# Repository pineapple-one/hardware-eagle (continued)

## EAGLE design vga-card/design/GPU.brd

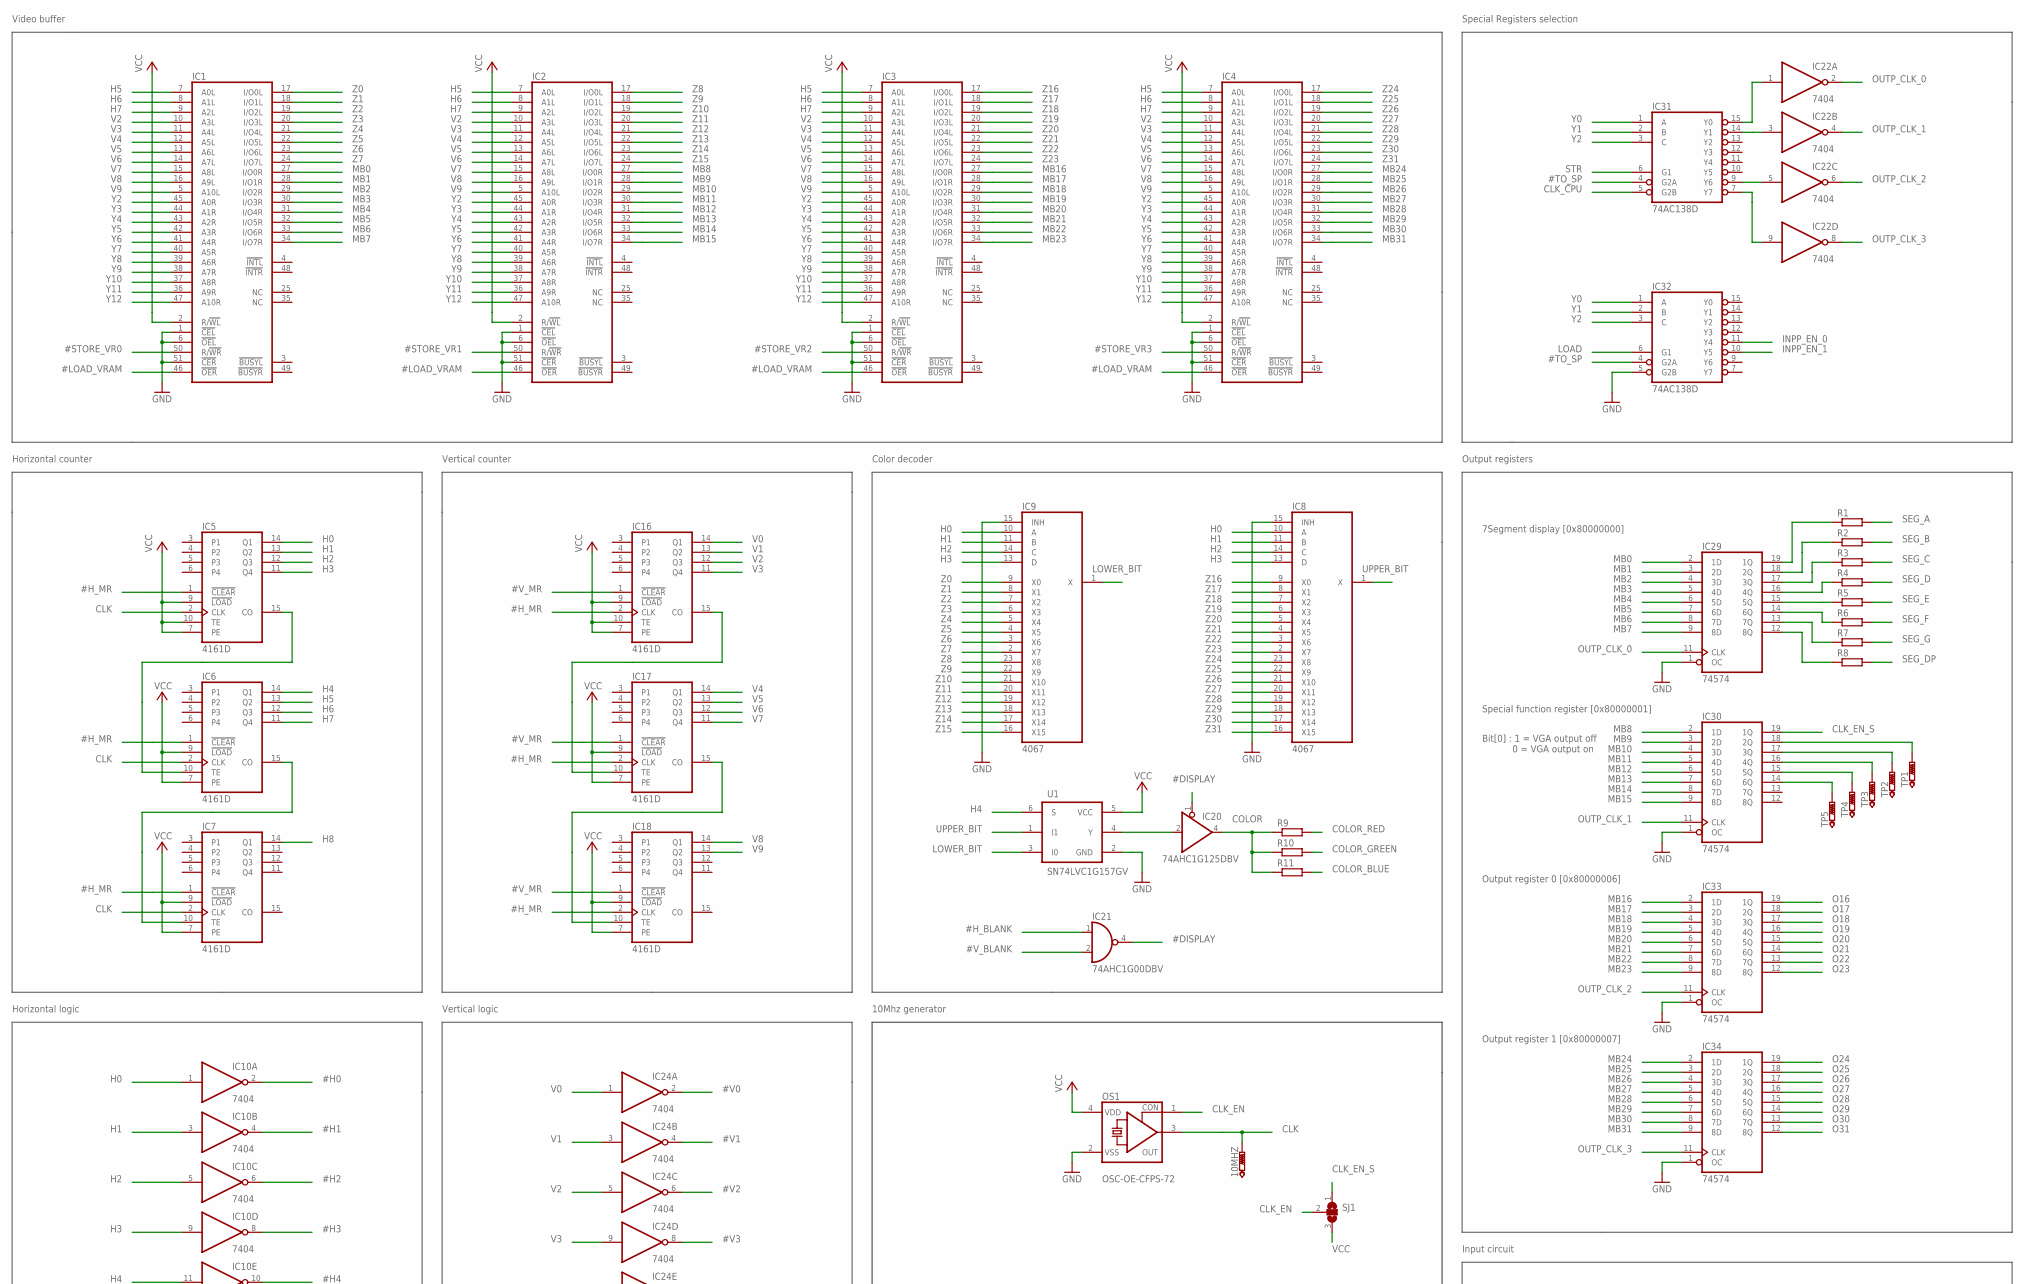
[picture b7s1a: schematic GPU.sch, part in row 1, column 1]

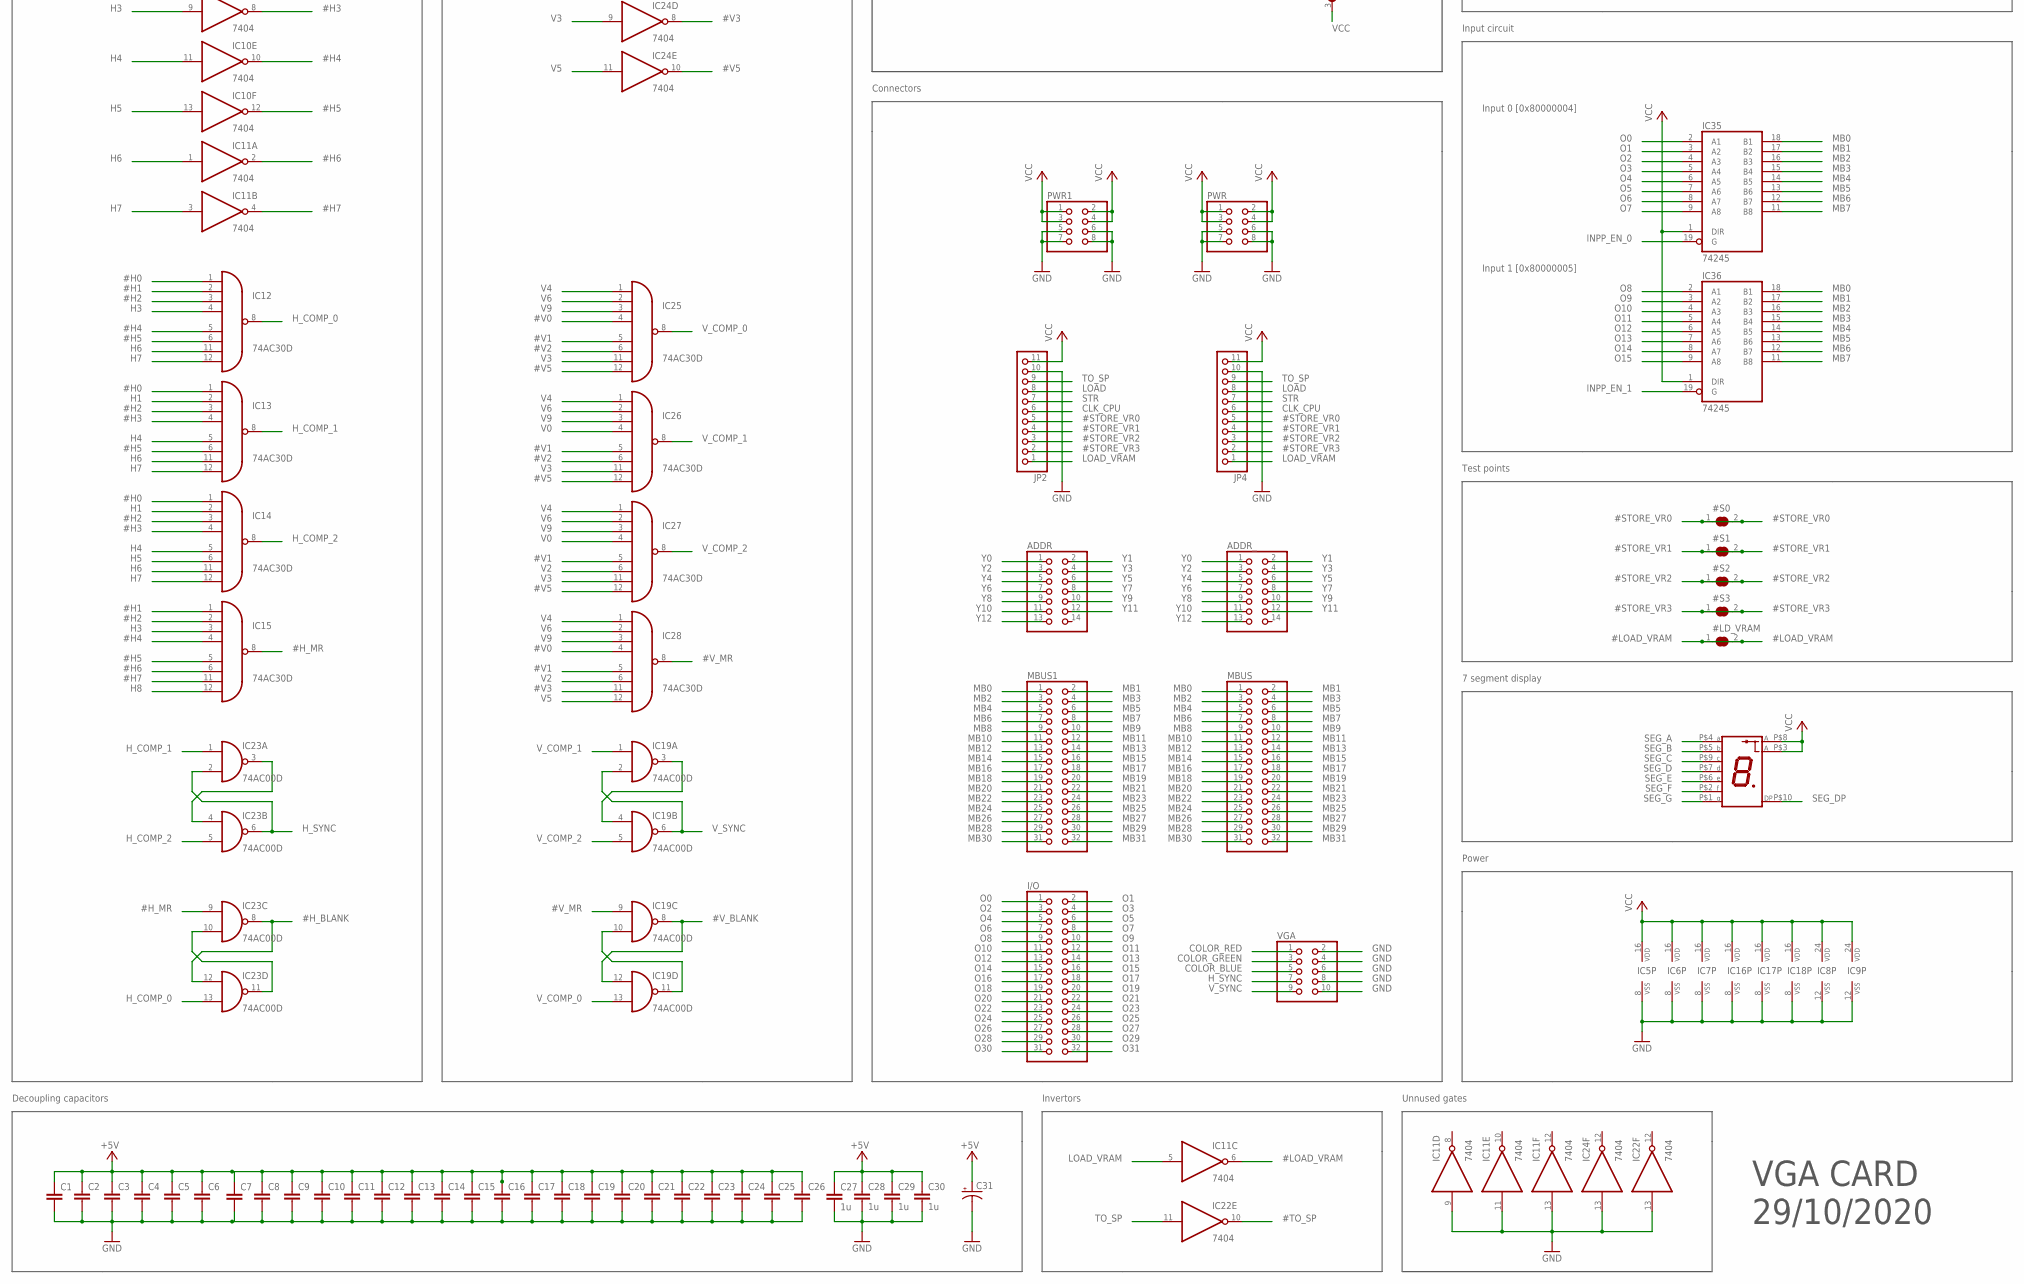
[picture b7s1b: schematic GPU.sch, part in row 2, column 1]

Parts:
10MHZ: PTR1B2,54; B2,54
#LD_VRAM: SJ
#S0, #S1, #S2, #S3: SJ
ADDR: PINHD-2X7; 2X07
ADDR_: PINHD-2X7; 2X07
C1, C2, C3, C4, C5, C6, C7, C8, C9, C10, C11, C12, C13, C14, C15, C16, C17, C18, C19, C20, C21, C22, C23, C24, C25, C26: C-EUC0805; C0805
C27, C28, C29, C30: 1u; C0805
C31: CAPACITOR-P153CLV-1010; 153CLV-1010
I/O: PINHD-2X16; 2X16
IC1, IC2, IC3, IC4: 71321L; L52-1
IC5, IC6, IC7, IC16, IC17, IC18: 4161D; SO16
IC8, IC9: 4067; TSSOP24
IC10, IC11, IC22, IC24: 7404; TSSOP14
IC12, IC13, IC14, IC15, IC25, IC26, IC27, IC28: 74AC30D; SO14
IC19, IC23: 74AC00D; SO14
IC20: 74AHC1G125DBV; SOT23-5
IC21: 74AHC1G00DBV; SOT23-5
IC29, IC30, IC33, IC34: 74574; TSSOP20
IC31, IC32: 74AC138D; SO16
IC35, IC36: 74245; TSSOP20
JP2, JP4: PINHD-1X11; 1X11
MBUS, MBUS1: PINHD-2X16; 2X16
OS1: OSC-OE-CFPS-72; 7.2X5.2-4-PAD
PWR, PWR1: PINHD-2X4; 2X04
R1, R2, R3, R4, R5, R6, R7, R8, R9, R10, R11: R-EU_R0805; R0805
SJ1: SJ2W; SJ_2
TP1, TP2, TP3, TP4, TP5: PTR1B1,27; B1,27
U1: SN74LVC1G157GV; SOT457
U$1: OPS-S5621YG
VGA: PINHD-2X5; 2X05

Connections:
#DISPLAY: IC20.1 (OE), IC21.4 (O)
#H0: IC10.2 (O), IC12.1 (I0), IC13.1 (I0), IC14.1 (I0)
#H1: IC10.4 (O), IC12.2 (I1), IC15.1 (I0)
#H2: IC10.6 (O), IC12.3 (I2), IC13.3 (I2), IC14.3 (I2), IC15.2 (I1)
#H3: IC10.8 (O), IC13.4 (I3), IC14.4 (I3)
#H4: IC10.10 (O), IC12.5 (I4), IC15.4 (I3)
#H5: IC10.12 (O), IC12.6 (I5), IC13.6 (I5), IC15.5 (I4)
#H6: IC11.2 (O), IC15.6 (I5)
#H7: IC11.4 (O), IC15.11 (I6)
#H_BLANK: IC21.1 (I0), IC23.8 (O), IC23.12 (I0)
#H_MR: IC5.1 (!CLEAR), IC6.1 (!CLEAR), IC7.1 (!CLEAR), IC15.8 (O), IC16.2 (CLK), IC17.2 (CLK), IC18.2 (CLK), IC23.9 (I0)
#LOAD_VRAM: #LD_VRAM.1, #LD_VRAM.2, IC1.46 (!OER), IC2.46 (!OER), IC3.46 (!OER), IC4.46 (!OER), IC11.6 (O)
#STORE_VR0: #S0.1, #S0.2, IC1.50 (R/!WR), JP2.5, JP4.5
#STORE_VR1: #S1.1, #S1.2, IC2.50 (R/!WR), JP2.4, JP4.4
#STORE_VR2: #S2.1, #S2.2, IC3.50 (R/!WR), JP2.3, JP4.3
#STORE_VR3: #S3.1, #S3.2, IC4.50 (R/!WR), JP2.2, JP4.2
#TO_SP: IC22.10 (O), IC31.4 (G2A), IC32.4 (G2A)
#V0: IC24.2 (O), IC25.4 (I3), IC28.4 (I3)
#V1: IC24.4 (O), IC25.5 (I4), IC26.5 (I4), IC27.5 (I4), IC28.5 (I4)
#V2: IC24.6 (O), IC25.6 (I5), IC26.6 (I5)
#V3: IC24.8 (O), IC28.11 (I6)
#V5: IC24.10 (O), IC25.12 (I7), IC26.12 (I7), IC27.12 (I7)
#V_BLANK: IC19.8 (O), IC19.12 (I0), IC21.2 (I1)
#V_MR: IC16.1 (!CLEAR), IC17.1 (!CLEAR), IC18.1 (!CLEAR), IC19.9 (I0), IC28.8 (O)
CLK: 10MHZ.TP, IC5.2 (CLK), IC6.2 (CLK), IC7.2 (CLK), OS1.3 (OUT)
CLK_CPU: IC31.5 (G2B), JP2.6, JP4.6
CLK_EN: OS1.1 (CON), SJ1.2
CLK_EN_S: IC30.19 (1Q), SJ1.1
COLOR: IC20.4 (O), R9.1, R10.1, R11.1
COLOR_BLUE: R11.2, VGA.5
COLOR_GREEN: R10.2, VGA.3
COLOR_RED: R9.2, VGA.1
GND: C1.2, C2.2, C3.2, C4.2, C5.2, C6.2, C7.2, C8.2, C9.2, C10.2, C11.2, C12.2, C13.2, C14.2, C15.2, C16.2, C17.2, C18.2, C19.2, C20.2, C21.2, C22.2, C23.2, C24.2, C25.2, C26.2, C27.2, C28.2, C29.2, C30.2, C31.-, IC1.1 (!CEL), IC1.6 (!OEL), IC1.26 (GND), IC1.51 (!CER), IC2.1 (!CEL), IC2.6 (!OEL), IC2.26 (GND), IC2.51 (!CER), IC3.1 (!CEL), IC3.6 (!OEL), IC3.26 (GND), IC3.51 (!CER), IC4.1 (!CEL), IC4.6 (!OEL), IC4.26 (GND), IC4.51 (!CER), IC5.8 (VSS), IC6.8 (VSS), IC7.8 (VSS), IC8.12 (VSS), IC8.15 (INH), IC9.12 (VSS), IC9.15 (INH), IC10.7 (GND), IC11.7 (GND), IC11.9 (I), IC11.11 (I), IC11.13 (I), IC12.7 (GND), IC13.7 (GND), IC14.7 (GND), IC15.7 (GND), IC16.8 (VSS), IC17.8 (VSS), IC18.8 (VSS), IC19.7 (GND), IC20.3 (GND), IC21.3 (GND), IC22.7 (GND), IC22.13 (I), IC23.7 (GND), IC24.7 (GND), IC24.13 (I), IC25.7 (GND), IC26.7 (GND), IC27.7 (GND), IC28.7 (GND), IC29.1 (OC), IC29.10 (GND), IC30.1 (OC), IC30.10 (GND), IC31.8 (GND), IC32.5 (G2B), IC32.8 (GND), IC33.1 (OC), IC33.10 (GND), IC34.1 (OC), IC34.10 (GND), IC35.10 (GND), IC36.10 (GND), JP2.10, JP4.10, OS1.2 (VSS), PWR.5, PWR.6, PWR.7, PWR.8, PWR1.5, PWR1.6, PWR1.7, PWR1.8, U1.2 (GND), VGA.2, VGA.4, VGA.6, VGA.8, VGA.10
H0: IC5.14 (Q1), IC8.10 (A), IC9.10 (A), IC10.1 (I)
H1: IC5.13 (Q2), IC8.11 (B), IC9.11 (B), IC10.3 (I), IC13.2 (I1), IC14.2 (I1)
H2: IC5.12 (Q3), IC8.14 (C), IC9.14 (C), IC10.5 (I)
H3: IC5.11 (Q4), IC8.13 (D), IC9.13 (D), IC10.9 (I), IC12.4 (I3), IC15.3 (I2)
H4: IC6.14 (Q1), IC10.11 (I), IC13.5 (I4), IC14.5 (I4), U1.6 (S)
H5: IC1.7 (A0L), IC2.7 (A0L), IC3.7 (A0L), IC4.7 (A0L), IC6.13 (Q2), IC10.13 (I), IC14.6 (I5)
H6: IC1.8 (A1L), IC2.8 (A1L), IC3.8 (A1L), IC4.8 (A1L), IC6.12 (Q3), IC11.1 (I), IC12.11 (I6), IC13.11 (I6), IC14.11 (I6)
H7: IC1.9 (A2L), IC2.9 (A2L), IC3.9 (A2L), IC4.9 (A2L), IC6.11 (Q4), IC11.3 (I), IC12.12 (I7), IC13.12 (I7), IC14.12 (I7)
H8: IC7.14 (Q1), IC15.12 (I7)
H_COMP_0: IC12.8 (O), IC23.13 (I1)
H_COMP_1: IC13.8 (O), IC23.1 (I0)
H_COMP_2: IC14.8 (O), IC23.5 (I1)
H_SYNC: IC23.2 (I1), IC23.6 (O), VGA.7
H_SYNC1: IC23.10 (I1), IC23.11 (O)
H_SYNC2: IC19.10 (I1), IC19.11 (O)
INPP_EN_0: IC32.11 (Y4), IC35.19 (G)
INPP_EN_1: IC32.10 (Y5), IC36.19 (G)
LOAD: IC32.6 (G1), JP2.8, JP4.8
LOAD_VRAM: IC11.5 (I), JP2.1, JP4.1
LOWER_BIT: IC9.1 (X), U1.3 (I0)
MB0: IC1.27 (I/O0R), IC29.2 (1D), IC35.18 (B1), IC36.18 (B1), MBUS.1, MBUS1.1
MB1: IC1.28 (I/O1R), IC29.3 (2D), IC35.17 (B2), IC36.17 (B2), MBUS.2, MBUS1.2
MB2: IC1.29 (I/O2R), IC29.4 (3D), IC35.16 (B3), IC36.16 (B3), MBUS.3, MBUS1.3
MB3: IC1.30 (I/O3R), IC29.5 (4D), IC35.15 (B4), IC36.15 (B4), MBUS.4, MBUS1.4
MB4: IC1.31 (I/O4R), IC29.6 (5D), IC35.14 (B5), IC36.14 (B5), MBUS.5, MBUS1.5
MB5: IC1.32 (I/O5R), IC29.7 (6D), IC35.13 (B6), IC36.13 (B6), MBUS.6, MBUS1.6
MB6: IC1.33 (I/O6R), IC29.8 (7D), IC35.12 (B7), IC36.12 (B7), MBUS.7, MBUS1.7
MB7: IC1.34 (I/O7R), IC29.9 (8D), IC35.11 (B8), IC36.11 (B8), MBUS.8, MBUS1.8
MB8: IC2.27 (I/O0R), IC30.2 (1D), MBUS.9, MBUS1.9
MB9: IC2.28 (I/O1R), IC30.3 (2D), MBUS.10, MBUS1.10
MB10: IC2.29 (I/O2R), IC30.4 (3D), MBUS.11, MBUS1.11
MB11: IC2.30 (I/O3R), IC30.5 (4D), MBUS.12, MBUS1.12
MB12: IC2.31 (I/O4R), IC30.6 (5D), MBUS.13, MBUS1.13
MB13: IC2.32 (I/O5R), IC30.7 (6D), MBUS.14, MBUS1.14
MB14: IC2.33 (I/O6R), IC30.8 (7D), MBUS.15, MBUS1.15
MB15: IC2.34 (I/O7R), IC30.9 (8D), MBUS.16, MBUS1.16
MB16: IC3.27 (I/O0R), IC33.2 (1D), MBUS.17, MBUS1.17
MB17: IC3.28 (I/O1R), IC33.3 (2D), MBUS.18, MBUS1.18
MB18: IC3.29 (I/O2R), IC33.4 (3D), MBUS.19, MBUS1.19
MB19: IC3.30 (I/O3R), IC33.5 (4D), MBUS.20, MBUS1.20
MB20: IC3.31 (I/O4R), IC33.6 (5D), MBUS.21, MBUS1.21
MB21: IC3.32 (I/O5R), IC33.7 (6D), MBUS.22, MBUS1.22
MB22: IC3.33 (I/O6R), IC33.8 (7D), MBUS.23, MBUS1.23
MB23: IC3.34 (I/O7R), IC33.9 (8D), MBUS.24, MBUS1.24
MB24: IC4.27 (I/O0R), IC34.2 (1D), MBUS.25, MBUS1.25
MB25: IC4.28 (I/O1R), IC34.3 (2D), MBUS.26, MBUS1.26
MB26: IC4.29 (I/O2R), IC34.4 (3D), MBUS.27, MBUS1.27
MB27: IC4.30 (I/O3R), IC34.5 (4D), MBUS.28, MBUS1.28
MB28: IC4.31 (I/O4R), IC34.6 (5D), MBUS.29, MBUS1.29
MB29: IC4.32 (I/O5R), IC34.7 (6D), MBUS.30, MBUS1.30
MB30: IC4.33 (I/O6R), IC34.8 (7D), MBUS.31, MBUS1.31
MB31: IC4.34 (I/O7R), IC34.9 (8D), MBUS.32, MBUS1.32
unnamed: IC23.3 (O), IC23.4 (I0)
unnamed: IC5.15 (CO), IC6.10 (TE)
unnamed: IC6.15 (CO), IC7.10 (TE)
unnamed: IC16.15 (CO), IC17.10 (TE)
unnamed: IC17.15 (CO), IC18.10 (TE)
unnamed: IC19.3 (O), IC19.4 (I0)
unnamed: IC20.2 (I), U1.4 (Y)
unnamed: IC22.1 (I), IC31.15 (Y0)
unnamed: IC30.18 (2Q), TP1.TP
unnamed: IC29.19 (1Q), R1.1
unnamed: IC22.9 (I), IC31.7 (Y7)
unnamed: IC29.18 (2Q), R2.1
unnamed: IC29.17 (3Q), R3.1
unnamed: IC29.16 (4Q), R4.1
unnamed: IC29.15 (5Q), R5.1
unnamed: IC29.14 (6Q), R6.1
unnamed: IC22.5 (I), IC31.9 (Y6)
unnamed: IC29.13 (7Q), R7.1
unnamed: IC29.12 (8Q), R8.1
unnamed: IC22.3 (I), IC31.14 (Y1)
unnamed: IC30.17 (3Q), TP2.TP
unnamed: IC30.16 (4Q), TP3.TP
unnamed: IC30.15 (5Q), TP4.TP
unnamed: IC30.14 (6Q), TP5.TP
O0: I/O.1, IC35.2 (A1)
O1: I/O.2, IC35.3 (A2)
O2: I/O.3, IC35.4 (A3)
O3: I/O.4, IC35.5 (A4)
O4: I/O.5, IC35.6 (A5)
O5: I/O.6, IC35.7 (A6)
O6: I/O.7, IC35.8 (A7)
O7: I/O.8, IC35.9 (A8)
O8: I/O.9, IC36.2 (A1)
O9: I/O.10, IC36.3 (A2)
O10: I/O.11, IC36.4 (A3)
O11: I/O.12, IC36.5 (A4)
O12: I/O.13, IC36.6 (A5)
O13: I/O.14, IC36.7 (A6)
O14: I/O.15, IC36.8 (A7)
O15: I/O.16, IC36.9 (A8)
O16: I/O.17, IC33.19 (1Q)
O17: I/O.18, IC33.18 (2Q)
O18: I/O.19, IC33.17 (3Q)
O19: I/O.20, IC33.16 (4Q)
O20: I/O.21, IC33.15 (5Q)
O21: I/O.22, IC33.14 (6Q)
O22: I/O.23, IC33.13 (7Q)
O23: I/O.24, IC33.12 (8Q)
O24: I/O.25, IC34.19 (1Q)
O25: I/O.26, IC34.18 (2Q)
O26: I/O.27, IC34.17 (3Q)
O27: I/O.28, IC34.16 (4Q)
O28: I/O.29, IC34.15 (5Q)
O29: I/O.30, IC34.14 (6Q)
O30: I/O.31, IC34.13 (7Q)
O31: I/O.32, IC34.12 (8Q)
OUTP_CLK_0: IC22.2 (O), IC29.11 (CLK)
OUTP_CLK_1: IC22.4 (O), IC30.11 (CLK)
OUTP_CLK_2: IC22.6 (O), IC33.11 (CLK)
OUTP_CLK_3: IC22.8 (O), IC34.11 (CLK)
SEG_A: R1.2, U$1.P$4 (A)
SEG_B: R2.2, U$1.P$5 (B)
SEG_C: R3.2, U$1.P$9 (C)
SEG_D: R4.2, U$1.P$7 (D)
SEG_DP: R8.2, U$1.P$10 (DP)
SEG_E: R5.2, U$1.P$6 (E)
SEG_F: R6.2, U$1.P$2 (F)
SEG_G: R7.2, U$1.P$1 (G)
STR: IC31.6 (G1), JP2.7, JP4.7
TO_SP: IC22.11 (I), JP2.9, JP4.9
UPPER_BIT: IC8.1 (X), U1.1 (I1)
V0: IC16.14 (Q1), IC24.1 (I), IC26.4 (I3), IC27.4 (I3)
V1: IC16.13 (Q2), IC24.3 (I)
V2: IC1.10 (A3L), IC2.10 (A3L), IC3.10 (A3L), IC4.10 (A3L), IC16.12 (Q3), IC24.5 (I), IC27.6 (I5), IC28.6 (I5)
V3: IC1.11 (A4L), IC2.11 (A4L), IC3.11 (A4L), IC4.11 (A4L), IC16.11 (Q4), IC24.9 (I), IC25.11 (I6), IC26.11 (I6), IC27.11 (I6)
V4: IC1.12 (A5L), IC2.12 (A5L), IC3.12 (A5L), IC4.12 (A5L), IC17.14 (Q1), IC25.1 (I0), IC26.1 (I0), IC27.1 (I0), IC28.1 (I0)
V5: IC1.13 (A6L), IC2.13 (A6L), IC3.13 (A6L), IC4.13 (A6L), IC17.13 (Q2), IC24.11 (I), IC28.12 (I7)
V6: IC1.14 (A7L), IC2.14 (A7L), IC3.14 (A7L), IC4.14 (A7L), IC17.12 (Q3), IC25.2 (I1), IC26.2 (I1), IC27.2 (I1), IC28.2 (I1)
V7: IC1.15 (A8L), IC2.15 (A8L), IC3.15 (A8L), IC4.15 (A8L), IC17.11 (Q4)
V8: IC1.16 (A9L), IC2.16 (A9L), IC3.16 (A9L), IC4.16 (A9L), IC18.14 (Q1)
V9: IC1.5 (A10L), IC2.5 (A10L), IC3.5 (A10L), IC4.5 (A10L), IC18.13 (Q2), IC25.3 (I2), IC26.3 (I2), IC27.3 (I2), IC28.3 (I2)
VCC: C1.1, C2.1, C3.1, C4.1, C5.1, C6.1, C7.1, C8.1, C9.1, C10.1, C11.1, C12.1, C13.1, C14.1, C15.1, C16.1, C17.1, C18.1, C19.1, C20.1, C21.1, C22.1, C23.1, C24.1, C25.1, C26.1, C27.1, C28.1, C29.1, C30.1, C31.+, IC1.2 (R/!WL), IC1.52 (VCC), IC2.2 (R/!WL), IC2.52 (VCC), IC3.2 (R/!WL), IC3.52 (VCC), IC4.2 (R/!WL), IC4.52 (VCC), IC5.7 (PE), IC5.9 (!LOAD), IC5.10 (TE), IC5.16 (VDD), IC6.7 (PE), IC6.9 (!LOAD), IC6.16 (VDD), IC7.7 (PE), IC7.9 (!LOAD), IC7.16 (VDD), IC8.24 (VDD), IC9.24 (VDD), IC10.14 (VCC), IC11.14 (VCC), IC12.14 (VCC), IC13.14 (VCC), IC14.14 (VCC), IC15.14 (VCC), IC16.7 (PE), IC16.9 (!LOAD), IC16.10 (TE), IC16.16 (VDD), IC17.7 (PE), IC17.9 (!LOAD), IC17.16 (VDD), IC18.7 (PE), IC18.9 (!LOAD), IC18.16 (VDD), IC19.14 (VCC), IC20.5 (VCC), IC21.5 (VCC), IC22.14 (VCC), IC23.14 (VCC), IC24.14 (VCC), IC25.14 (VCC), IC26.14 (VCC), IC27.14 (VCC), IC28.14 (VCC), IC29.20 (VCC), IC30.20 (VCC), IC31.16 (VCC), IC32.16 (VCC), IC33.20 (VCC), IC34.20 (VCC), IC35.1 (DIR), IC35.20 (VCC), IC36.1 (DIR), IC36.20 (VCC), JP2.11, JP4.11, OS1.4 (VDD), PWR.1, PWR.2, PWR.3, PWR.4, PWR1.1, PWR1.2, PWR1.3, PWR1.4, SJ1.3, U1.5 (VCC), U$1.P$3 (A), U$1.P$8 (A)
V_COMP_0: IC19.13 (I1), IC25.8 (O)
V_COMP_1: IC19.1 (I0), IC26.8 (O)
V_COMP_2: IC19.5 (I1), IC27.8 (O)
V_SYNC: IC19.2 (I1), IC19.6 (O), VGA.9
Y0: ADDR.1, ADDR_.1, IC31.1 (A), IC32.1 (A)
Y1: ADDR.2, ADDR_.2, IC31.2 (B), IC32.2 (B)
Y2: ADDR.3, ADDR_.3, IC1.45 (A0R), IC2.45 (A0R), IC3.45 (A0R), IC4.45 (A0R), IC31.3 (C), IC32.3 (C)
Y3: ADDR.4, ADDR_.4, IC1.44 (A1R), IC2.44 (A1R), IC3.44 (A1R), IC4.44 (A1R)
Y4: ADDR.5, ADDR_.5, IC1.43 (A2R), IC2.43 (A2R), IC3.43 (A2R), IC4.43 (A2R)
Y5: ADDR.6, ADDR_.6, IC1.42 (A3R), IC2.42 (A3R), IC3.42 (A3R), IC4.42 (A3R)
Y6: ADDR.7, ADDR_.7, IC1.41 (A4R), IC2.41 (A4R), IC3.41 (A4R), IC4.41 (A4R)
Y7: ADDR.8, ADDR_.8, IC1.40 (A5R), IC2.40 (A5R), IC3.40 (A5R), IC4.40 (A5R)
Y8: ADDR.9, ADDR_.9, IC1.39 (A6R), IC2.39 (A6R), IC3.39 (A6R), IC4.39 (A6R)
Y9: ADDR.10, ADDR_.10, IC1.38 (A7R), IC2.38 (A7R), IC3.38 (A7R), IC4.38 (A7R)
Y10: ADDR.11, ADDR_.11, IC1.37 (A8R), IC2.37 (A8R), IC3.37 (A8R), IC4.37 (A8R)
Y11: ADDR.12, ADDR_.12, IC1.36 (A9R), IC2.36 (A9R), IC3.36 (A9R), IC4.36 (A9R)
Y12: ADDR.13, ADDR_.13, IC1.47 (A10R), IC2.47 (A10R), IC3.47 (A10R), IC4.47 (A10R)
Z0: IC1.17 (I/O0L), IC9.9 (X0)
Z1: IC1.18 (I/O1L), IC9.8 (X1)
Z2: IC1.19 (I/O2L), IC9.7 (X2)
Z3: IC1.20 (I/O3L), IC9.6 (X3)
Z4: IC1.21 (I/O4L), IC9.5 (X4)
Z5: IC1.22 (I/O5L), IC9.4 (X5)
Z6: IC1.23 (I/O6L), IC9.3 (X6)
Z7: IC1.24 (I/O7L), IC9.2 (X7)
Z8: IC2.17 (I/O0L), IC9.23 (X8)
Z9: IC2.18 (I/O1L), IC9.22 (X9)
Z10: IC2.19 (I/O2L), IC9.21 (X10)
Z11: IC2.20 (I/O3L), IC9.20 (X11)
Z12: IC2.21 (I/O4L), IC9.19 (X12)
Z13: IC2.22 (I/O5L), IC9.18 (X13)
Z14: IC2.23 (I/O6L), IC9.17 (X14)
Z15: IC2.24 (I/O7L), IC9.16 (X15)
Z16: IC3.17 (I/O0L), IC8.9 (X0)
Z17: IC3.18 (I/O1L), IC8.8 (X1)
Z18: IC3.19 (I/O2L), IC8.7 (X2)
Z19: IC3.20 (I/O3L), IC8.6 (X3)
Z20: IC3.21 (I/O4L), IC8.5 (X4)
Z21: IC3.22 (I/O5L), IC8.4 (X5)
Z22: IC3.23 (I/O6L), IC8.3 (X6)
Z23: IC3.24 (I/O7L), IC8.2 (X7)
Z24: IC4.17 (I/O0L), IC8.23 (X8)
Z25: IC4.18 (I/O1L), IC8.22 (X9)
Z26: IC4.19 (I/O2L), IC8.21 (X10)
Z27: IC4.20 (I/O3L), IC8.20 (X11)
Z28: IC4.21 (I/O4L), IC8.19 (X12)
Z29: IC4.22 (I/O5L), IC8.18 (X13)
Z30: IC4.23 (I/O6L), IC8.17 (X14)
Z31: IC4.24 (I/O7L), IC8.16 (X15)

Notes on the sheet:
Video buffer
Horizontal counter
Vertical counter
Color decoder
Horizontal logic
Vertical logic
10Mhz generator
Connectors
Test points
Special Registers selection
Output registers
7Segment display [0x80000000]
Special function register [0x80000001]
Output register 0 [0x80000006]
Output register 1 [0x80000007]
Bit[0] : 1 = VGA output off 0 = VGA output on
Input circuit
Input 0 [0x80000004]
Input 1 [0x80000005]
7 segment display
Power
Decoupling capacitors
Invertors
Unnused gates
VGA CARD 29/10/2020

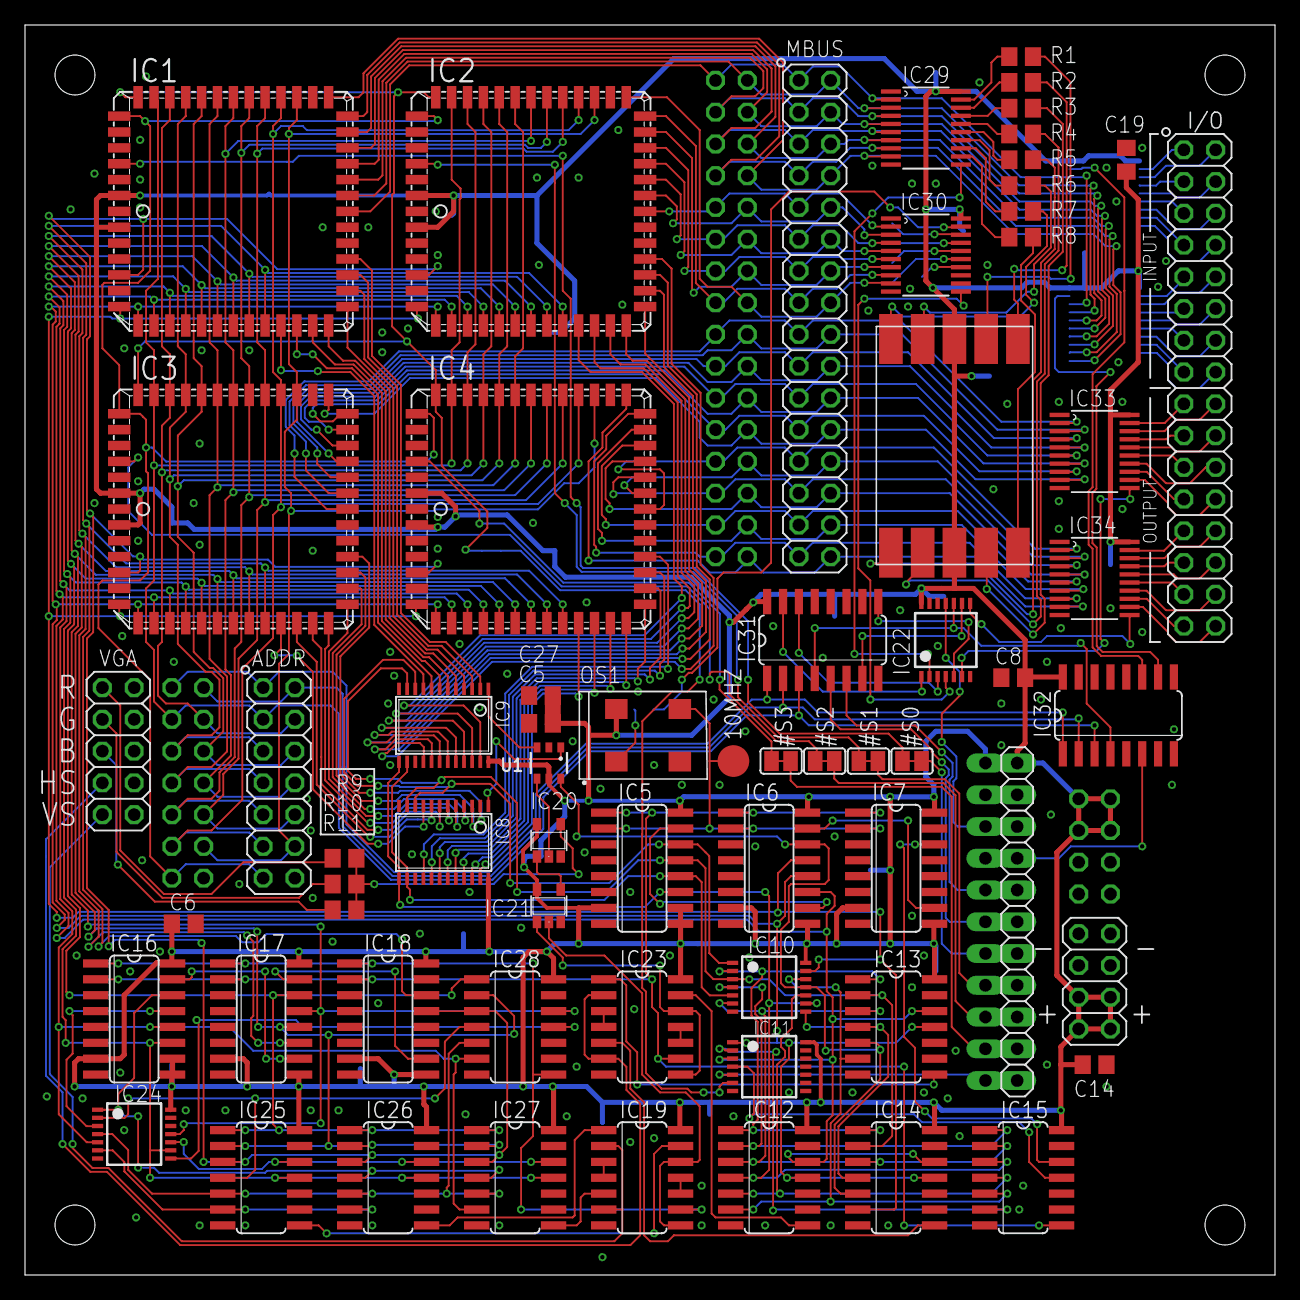
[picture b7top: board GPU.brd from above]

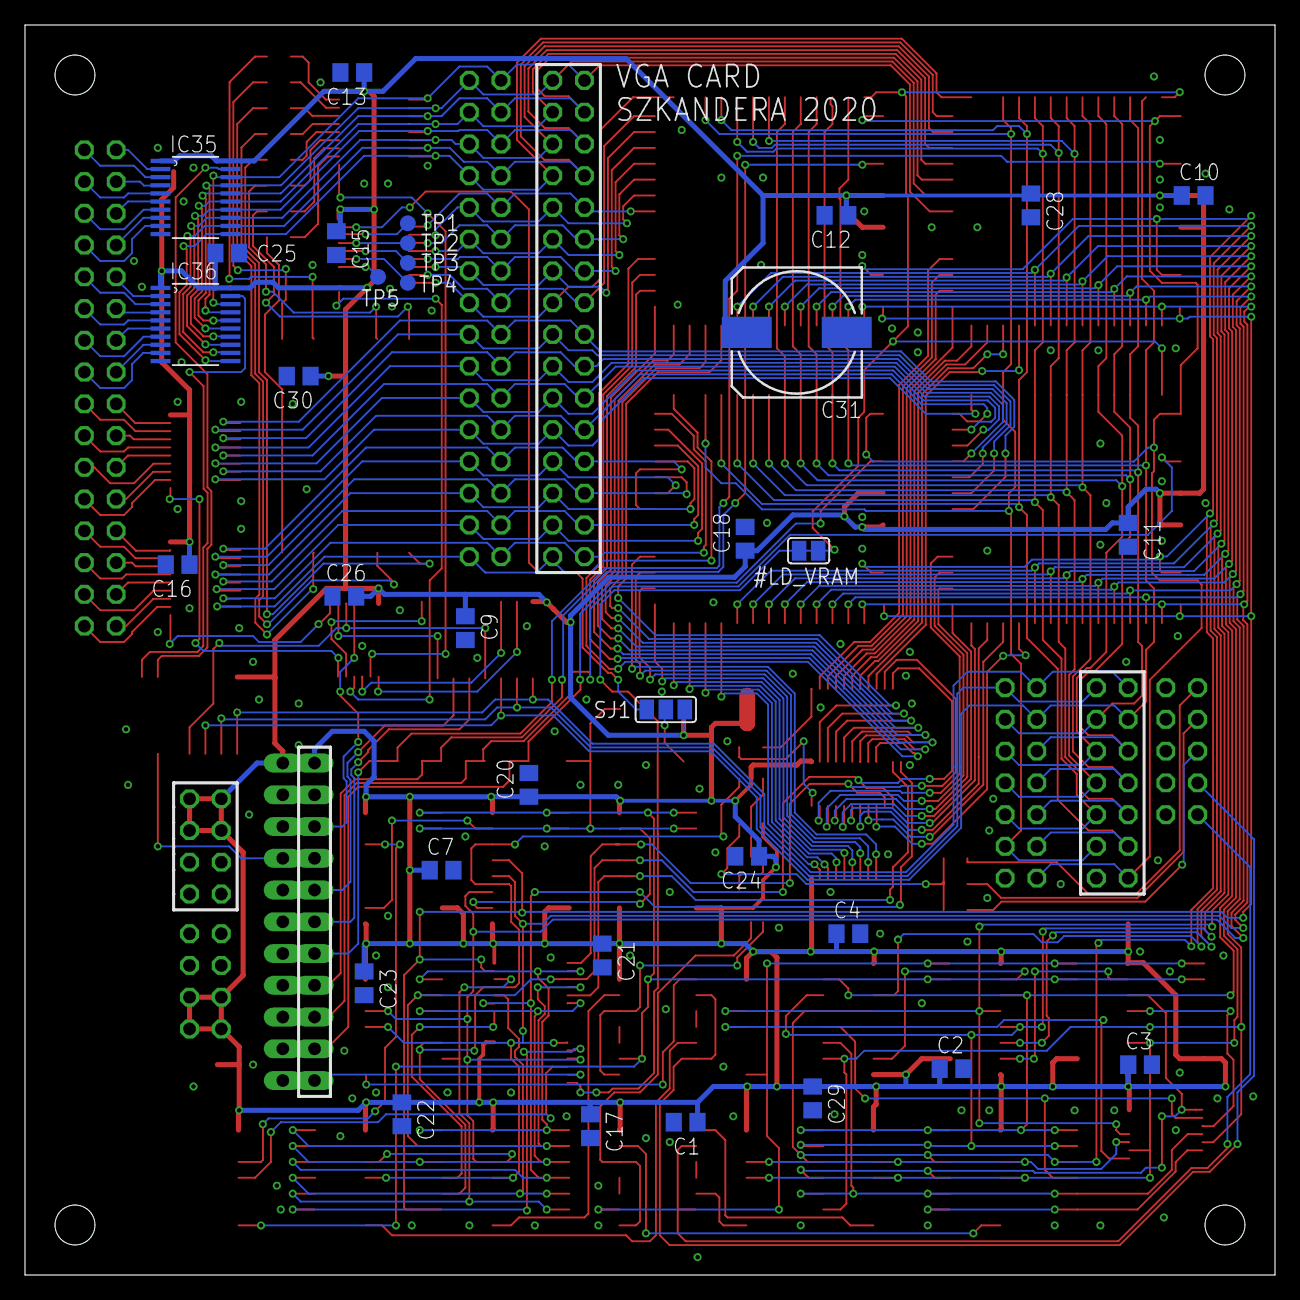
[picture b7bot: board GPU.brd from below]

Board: 2 copper layers, 100.0 x 100.0 mm, 103 parts (34 on the bottom side), 216 nets.
